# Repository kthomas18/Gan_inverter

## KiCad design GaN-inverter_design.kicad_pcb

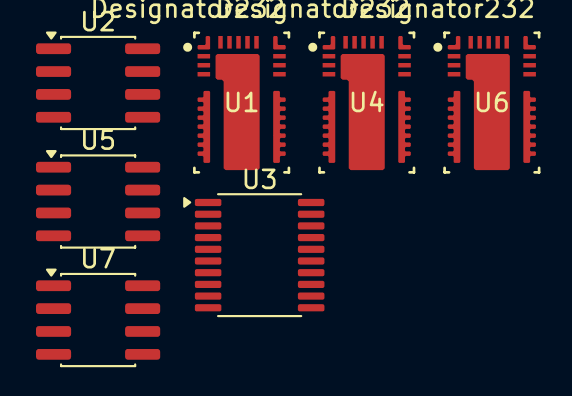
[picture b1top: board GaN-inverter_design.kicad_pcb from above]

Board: 2 copper layers, 7 parts (0 on the bottom side), 7 nets, no tracks yet.

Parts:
U1, U4, U6: LMG2100R026VBNR; VBN0018A-MFG
U2, U5, U7: INA240A1D; SOIC-8_3.9x4.9mm_P1.27mm
U3: SN74LVC245APW; TSSOP-20_4.4x6.5mm_P0.65mm

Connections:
+5V: U2.6 (V+), U5.6 (V+), U7.6 (V+)
+24V: U1.7 (VIN), U4.7 (VIN), U6.7 (VIN)
GND: U1.6 (PGND), U1.15 (AGND), U1.17 (PGND), U1.18 (PGND), U2.2 (GND), U2.4 (GND), U4.6 (PGND), U4.15 (AGND), U4.17 (PGND), U4.18 (PGND), U5.2 (GND), U5.4 (GND), U6.6 (PGND), U6.15 (AGND), U6.17 (PGND), U6.18 (PGND), U7.2 (GND), U7.4 (GND)
unnamed: U1.5 (SW), U2.1 (-)
unnamed: U4.5 (SW), U5.1 (-)
unnamed: U6.5 (SW), U7.1 (-)
VCC: U2.3 (REF2), U2.7 (REF1), U5.3 (REF2), U5.7 (REF1), U7.3 (REF2), U7.7 (REF1)

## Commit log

2026-01-19 initial kicad project
